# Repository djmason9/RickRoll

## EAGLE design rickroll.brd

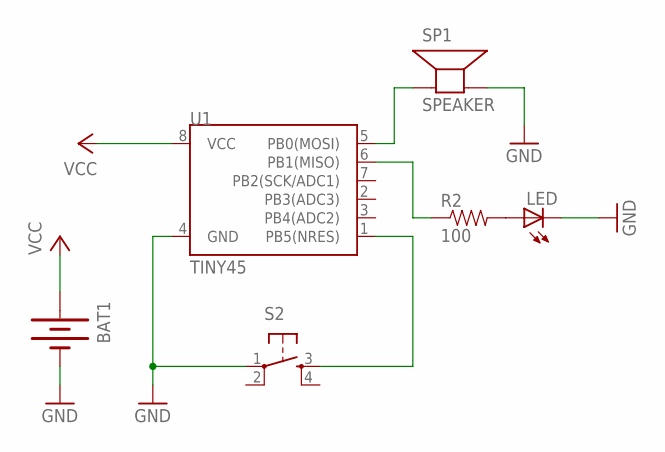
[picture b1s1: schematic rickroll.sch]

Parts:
BAT1: BATTERY20PTH; BATTCOM_20MM_PTH
LED: LEDCHIPLED_0805; CHIPLED_0805
R2: 100; 0603-RES
S2: TAC_SWITCHPTH; TACTILE-PTH
SP1: SPEAKER; AL60P
U1: TINY45; DIP08

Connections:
GND: BAT1.2 (-), LED.C, S2.1, SP1.2 (-), U1.4 (GND)
unnamed: S2.3, U1.1 (PB5(NRES))
unnamed: SP1.1 (+), U1.5 (PB0(MOSI))
unnamed: R2.1, U1.6 (PB1(MISO))
unnamed: LED.A, R2.2
VCC: BAT1.1 (+), U1.8 (VCC)

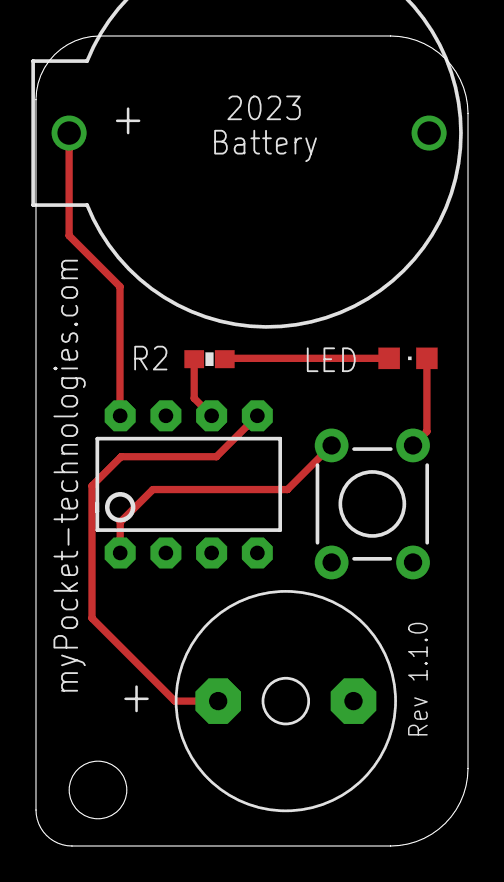
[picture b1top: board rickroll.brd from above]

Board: 2 copper layers, 24.0 x 45.0 mm, 7 parts (1 on the bottom side), 6 nets.

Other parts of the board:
U$1: RICK

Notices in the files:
parts and their libraries:
SparkFun-DigitalIC: Licensing: CC v3.0 Share-Alike You are welcome to use this library for commercial purposes.
